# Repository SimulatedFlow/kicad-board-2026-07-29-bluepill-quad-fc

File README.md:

# 2026-07-29-bluepill-quad-fc

<!-- SF-STORE-BLOCK:BEGIN -->
## 🛒 Source-available — see before you buy

This repository contains the **full design files** of a commercial hardware board. It is **source-available, not open source**: read it, evaluate it, then buy a license to use it. See **LICENSE.md (source-available, purchase required)**.

**Get it / Buy:**
- eBay store — all our boards and PCB art: https://www.ebay.de/usr/simula-9
- Merch shop (dev & gaming): https://simulatedflow.myspreadshop.de
- Merch shop (Synthetica / EDM): https://synthetica.myspreadshop.de
- Direct / invoice (Simulated Flow UG): simulatedflow@gmail.com

_This board has no eBay item number of its own listed here — the store link above holds all current listings._

### 📬 **Free Board Documentation & Firmware Pack**

Schematics, BOMs and example-firmware docs for our STM32 carrier boards. Get it by joining the newsletter — plus a heads-up when something new ships. Double opt-in, unsubscribe in one click, no address sharing.

👉 **[Get the free pack](https://simulatedflow.teufel-engineering.com/newsletter/hardware/?q=gh)**

_© 2026 Simulated Flow UG. All rights reserved._
<!-- SF-STORE-BLOCK:END -->

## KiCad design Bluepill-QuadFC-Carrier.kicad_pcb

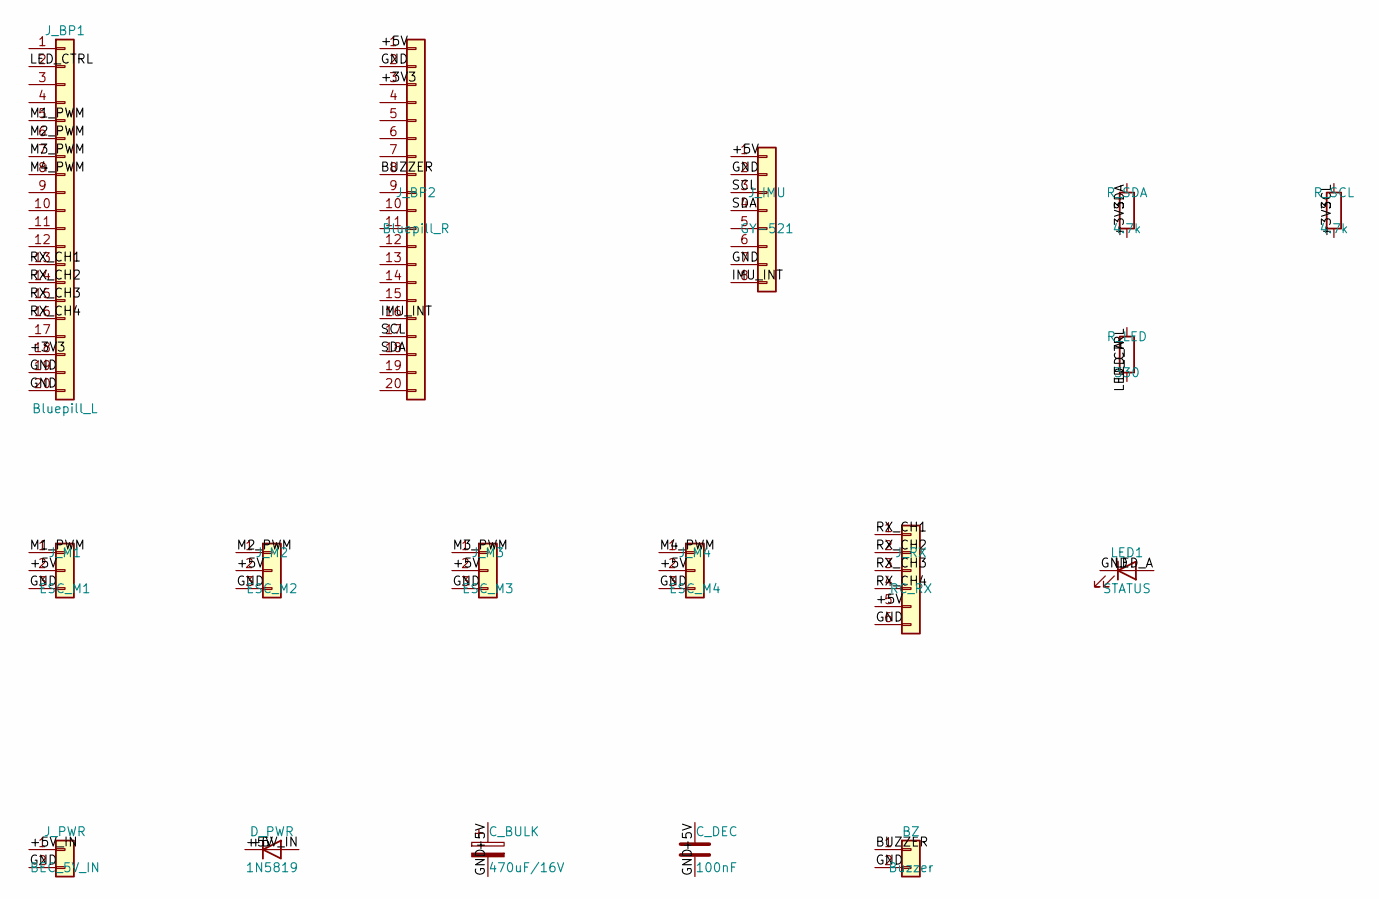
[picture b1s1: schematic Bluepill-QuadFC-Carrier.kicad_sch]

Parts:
BZ: Buzzer; PinHeader_1x02_P2.54mm_Vertical
C_BULK: 470uF/16V; CP_Radial_D8.0mm_P3.50mm
C_DEC: 100nF; C_Disc_D3.0mm_W1.6mm_P2.50mm
D_PWR: 1N5819; D_DO-41_SOD81_P10.16mm_Horizontal
J_BP1: Bluepill_L; PinSocket_1x20_P2.54mm_Vertical
J_BP2: Bluepill_R; PinSocket_1x20_P2.54mm_Vertical
J_IMU: GY-521; PinSocket_1x08_P2.54mm_Vertical
J_M1: ESC_M1; PinHeader_1x03_P2.54mm_Vertical
J_M2: ESC_M2; PinHeader_1x03_P2.54mm_Vertical
J_M3: ESC_M3; PinHeader_1x03_P2.54mm_Vertical
J_M4: ESC_M4; PinHeader_1x03_P2.54mm_Vertical
J_PWR: BEC_5V_IN; TerminalBlock_Phoenix_MKDS-1,5-2-5.08_1x02_P5.08mm_Horizont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
J_RX: RC_RX; PinHeader_1x06_P2.54mm_Vertical
LED1: STATUS; LED_D5.0mm
R_LED: 330; R_Axial_DIN0207_L6.3mm_D2.5mm_P7.62mm_Horizontal
R_SCL: 4.7k; R_Axial_DIN0207_L6.3mm_D2.5mm_P7.62mm_Horizontal
R_SDA: 4.7k; R_Axial_DIN0207_L6.3mm_D2.5mm_P7.62mm_Horizontal

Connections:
+3V3: J_BP1.18, J_BP2.3, R_SCL.2, R_SDA.2
+5V: C_BULK.1, C_DEC.1, D_PWR.1 (K), J_BP2.1, J_IMU.1, J_M1.2, J_M2.2, J_M3.2, J_M4.2, J_RX.5
+5V_IN: D_PWR.2 (A), J_PWR.1
BUZZER: BZ.1, J_BP2.8
GND: BZ.2, C_BULK.2, C_DEC.2, J_BP1.19, J_BP1.20, J_BP2.2, J_IMU.2, J_IMU.7, J_M1.3, J_M2.3, J_M3.3, J_M4.3, J_PWR.2, J_RX.6, LED1.1 (K)
IMU_INT: J_BP2.16, J_IMU.8
LED_A: LED1.2 (A), R_LED.2
LED_CTRL: J_BP1.2, R_LED.1
M1_PWM: J_BP1.5, J_M1.1
M2_PWM: J_BP1.6, J_M2.1
M3_PWM: J_BP1.7, J_M3.1
M4_PWM: J_BP1.8, J_M4.1
RX_CH1: J_BP1.13, J_RX.1
RX_CH2: J_BP1.14, J_RX.2
RX_CH3: J_BP1.15, J_RX.3
RX_CH4: J_BP1.16, J_RX.4
SCL: J_BP2.17, J_IMU.3, R_SCL.1
SDA: J_BP2.18, J_IMU.4, R_SDA.1

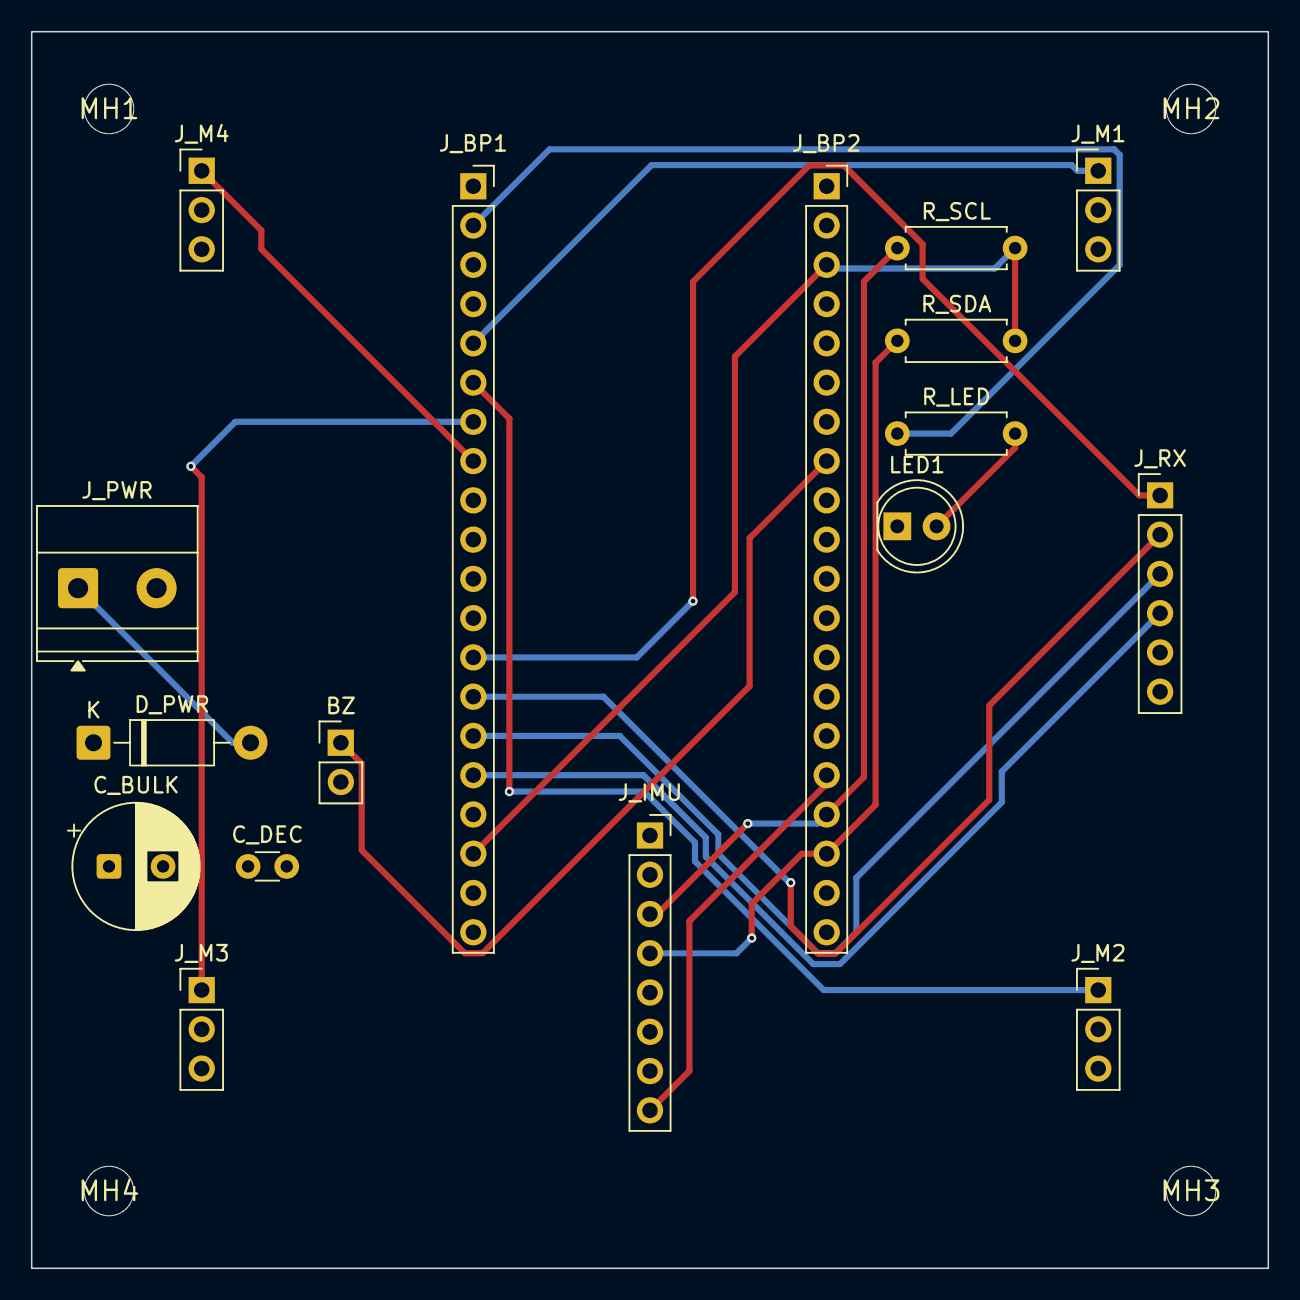
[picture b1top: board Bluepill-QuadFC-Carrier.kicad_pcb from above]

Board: 4 copper layers, 80.0 x 80.0 mm, 21 parts (0 on the bottom side), 18 nets.

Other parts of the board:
MH1, MH2, MH3, MH4: MountingHole_3.2mm
